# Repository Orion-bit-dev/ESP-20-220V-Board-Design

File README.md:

# 220V Power Monitor (ESP32)

An ESP32 project that switches two 220 V lamps with push buttons and a live web page, senses an outside 220 V power source, keeps working when WiFi drops, and lets me save a new WiFi network from my phone.

Built as part of my learning in programming and electronics. It builds on two earlier projects: a basic power monitor and a power-sensing relay with a web page.

---

## ⚠️ Safety first (220 V)

This project involves mains voltage, which can seriously injure or kill.

- **Never put 220 V on the breadboard or near the ESP32 and OLED.** Use the screw terminals of the relay modules only.
- Keep the whole 220 V side in a **closed enclosure**, with a **fuse or breaker** before it.
- Have a **qualified electrician** make the 220 V connections. Switch the power off at the breaker before touching anything.
- The ESP32 side runs at only 3.3 V and 5 V. That is the part I built myself.

---

## Features

- **Two relay outputs** switch two 220 V lamps (LED 1 and LED 2).
- **Physical push buttons** toggle each relay.
- **Live web page** shows the full state and refreshes every second (`/status` endpoint returning JSON).
- **OLED display** (I2C) shows the same state, plus the IP address for 3 seconds at boot.
- **Mains sensing** of an outside 220 V source ("Power 2") using an isolated supply and an opto module.
- **WiFi that doesn't freeze the device:** a non-blocking `millis()` timer reconnects every 15 seconds, so the buttons always work, even offline.
- **WiFi setup mode:** if no WiFi is saved, or I hold the setup button for 3 seconds, the ESP32 creates its own network (`ESP32_Setup`). I join it from my phone, open `192.168.4.1`, enter the new WiFi, and it saves to flash and restarts.
- **Admin password** required for the web Toggle buttons, since they switch 220 V.

### LED logic

| LED | Turns on when |
|---|---|
| LED 1 | Relay A is on **or** Power 2 is present |
| LED 2 | Relay B is on |

---

## Hardware

- ESP32 dev board
- 2 × 5 V relay modules (active low)
- 2 × push buttons (Relay A, Relay B) + 1 × setup button
- SSD1306 OLED, 128×64, I2C
- 100 µF capacitor
- HLK-PM01 (isolated 220 V to 5 V module)
- Opto-isolator module
- Fuse, enclosure, and two 220 V lamps

### Pin map (ESP32 side)

| Part | ESP32 pin |
|---|---|
| Relay A `IN` | D18 (relay `VCC` to VIN, `GND` to GND) |
| Relay B `IN` | D19 |
| Button A | D25 and GND |
| Button B | D26 and GND |
| Setup button | D32 and GND |
| Opto module output (Power 2 sense) | D27 and GND (LOW = present) |
| OLED | SDA D21, SCL D22, VCC 3V3, GND |
| Capacitor 100 µF | across 3V3 and GND (stripe leg to GND) |

### Sensing an outside 220 V source safely

```
220 V (Power 2) -> fuse -> HLK-PM01 (isolated 5 V module) -> opto module input (IN+ / IN-)
opto module output -> ESP32 D27 and GND
```

- Opto module jumper **ON** (3–12 V input).
- The HLK output minus goes **only to the opto IN-**, never to the ESP32 GND. The opto module is the isolation bridge.
- Do **not** use a bare opto module directly on 220 V, and never use a resistor or capacitor dropper supply.
- Alternative: a relay with a 220 V coil, with its dry contact wired to D27 and GND like a switch.

---

## Software

### Requirements

- Arduino IDE with the ESP32 board package
- Libraries: `Adafruit GFX Library` and `Adafruit SSD1306`
- Built-in ESP32 libraries used: `WiFi`, `WebServer`, `Preferences`, `Wire`

### Setup

1. Open `power_monitor_220v.ino` in the Arduino IDE.
2. **Change the placeholder passwords** at the top of the sketch:
   - `apPass`: the password of the setup WiFi (8 characters or more)
   - `adminPass`: the password needed for the web Toggle buttons
3. Select your ESP32 board and upload.
4. On first boot there is no saved WiFi, so the OLED shows **WIFI SETUP MODE**. Connect your phone to `ESP32_Setup`, open `192.168.4.1`, enter your WiFi name and password, and tap **Save & Reboot**.
5. After reboot, the OLED shows the IP address. Open it in a browser to see the live page.

> Never commit real WiFi names or passwords to a public repository.

### Web endpoints

| Endpoint | Method | Purpose |
|---|---|---|
| `/` | GET | Live status page (or the WiFi form in setup mode) |
| `/status` | GET | Current state as JSON |
| `/toggleA`, `/toggleB` | POST | Toggle a relay (needs the admin password) |
| `/savewifi` | POST | Save a new WiFi (works only in setup mode) |

---

## Security fixes from my first version

- Removed the fallback WiFi name and password from the code. With nothing saved, the device goes straight to setup mode.
- `/savewifi` now works only in setup mode. Before, anyone on my WiFi could overwrite my settings.
- The web Toggle buttons need the admin password, because they switch 220 V.
- Holding the setup button no longer restarts setup mode repeatedly.
- The OLED now also updates when I toggle from the web page.

---

## Test checklist

| Check | Expected result |
|---|---|
| Nothing saved yet | OLED shows WIFI SETUP MODE |
| Boot with saved WiFi | "Connecting to WiFi", then the IP for 3 s, then the normal screen |
| Web page | Updates every second, no `?` shown |
| Buttons A and B | Relay clicks, web page and OLED follow |
| Web Toggle, wrong admin password | "Not allowed", relay does not move |
| Web Toggle, right admin password | Relay toggles, OLED follows |
| Power 2 on and off | LED 1 follows, Serial prints the change |
| Router off for 15 s, then on | Serial prints "WiFi dropped!", then it reconnects |
| Hold setup button for 3 s | OLED shows setup instructions, relays turn off |
| Save a new WiFi in setup mode | Restarts and joins it |
| `/savewifi` in normal mode | "Only in setup mode" |
| Unplug and plug back in | Remembers the saved WiFi |

---

## What I learned

- **OLED static at boot:** the WiFi power spike crashed the screen. Fixed with a 100 µF capacitor and calling `display.begin()` again after the WiFi attempt.
- **Never use `WiFi.mode(WIFI_OFF)`:** it crashed my ESP32 (`xQueueSemaphoreTake`). Use `WIFI_STA` or `WIFI_AP` instead, and let the buttons work offline.
- **No `while` loop without a `millis()` timeout:** the ESP32 freezes if the router is off.
- **Active-low relays:** "off" means letting go of the pin (`OUTPUT_OPEN_DRAIN` with HIGH). A normal `digitalWrite(HIGH)` left the relay stuck on.
- **The web page `?` bug:** switching to `XMLHttpRequest` fixed it for me. `fetch()` worked on an earlier page, so the real cause is not proven and is worth testing again.
- **Keep secrets out of code:** I once had my real WiFi password in a sketch. Secrets don't belong in code, notes, or chats.

---

## Roadmap

- [ ] Add a password to the `/savewifi` page and show the IP in the setup screen
- [ ] Draw the schematic in KiCad, with a mains block (fuse, HLK-PM01) separated from the low-voltage block (opto module, relays, ESP32)
- [ ] Add photos of the build and wiring

---

## Disclaimer

This is a learning project, provided as is. Working with mains voltage is dangerous. Always involve a qualified electrician for the 220 V side, and use this at your own risk.

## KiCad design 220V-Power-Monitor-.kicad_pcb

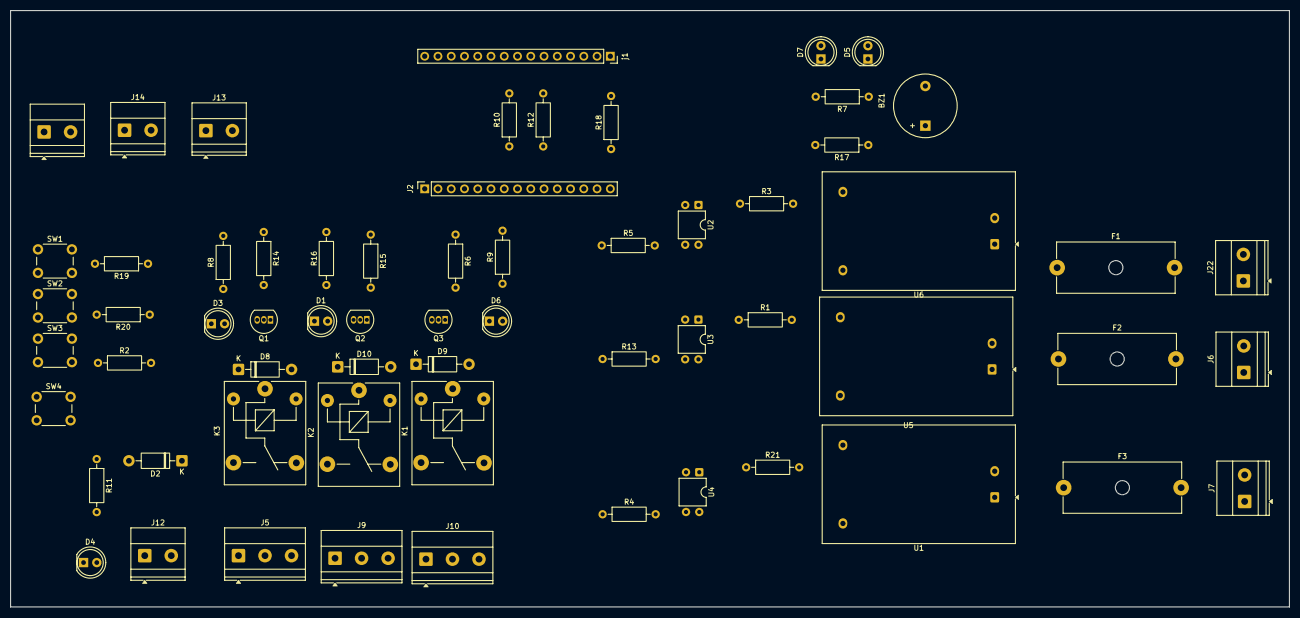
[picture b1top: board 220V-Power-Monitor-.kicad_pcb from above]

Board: 2 copper layers, 245.0 x 114.2 mm, 63 parts (0 on the bottom side), 52 nets, no tracks yet.

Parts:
BZ1: Buzzer; Buzzer_12x9.5RM7.6
D1, D3, D4, D5, D6, D7: LED; LED_D5.0mm
D2, D8, D9, D10: D; D_DO-41_SOD81_P10.16mm_Horizontal
F1, F2, F3: Fuse; Fuseholder_Cylinder-5x20mm_Schurter_0031_8201_Horizontal_Op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
J2: ESP32_left_row; PinSocket_1x15_P2.54mm_Vertical
J5, J9, J10: Screw_Terminal_01x03; TerminalBlock_Phoenix_MKDS-1,5-3-5.08_1x03_P5.08mm_Horizont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
J6, J7, J8, J12, J13, J14, J22: Screw_Terminal_01x02; TerminalBlock_Phoenix_MKDS-1,5-2-5.08_1x02_P5.08mm_Horizont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
K1, K2, K3: Relay_SPDT; Relay_SPDT_SANYOU_SRD_Series_Form_C
Q1, Q2, Q3: BC337; TO-92_Inline
R1, R2, R3, R19, R20, R21: 470; R_Axial_DIN0207_L6.3mm_D2.5mm_P10.16mm_Horizontal
R4, R5, R6, R13, R14, R15: 10k; R_Axial_DIN0207_L6.3mm_D2.5mm_P10.16mm_Horizontal
R7, R8, R9, R16, R17: 330; R_Axial_DIN0207_L6.3mm_D2.5mm_P10.16mm_Horizontal
R10, R11, R12, R18: 1k; R_Axial_DIN0207_L6.3mm_D2.5mm_P10.16mm_Horizontal
SW1, SW2, SW3, SW4: SW_Push; SW_PUSH_6mm
U1, U5, U6: HLK-PM01; Converter_ACDC_Hi-Link_HLK-PMxx
U2, U3, U4: PC817; DIP-4_W7.62mm
j1: ESP32_right_row; PinSocket_1x15_P2.54mm_Vertical

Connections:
/GND_ESP: BZ1.2 (-), D1.1 (K), D3.1 (K), D4.1 (K), D5.1 (K), D6.1 (K), D7.1 (K), J2.14, J8.2, J12.2, J13.2, J14.1, Q1.3 (E), Q2.3 (E), Q3.3 (E), R6.1, R14.1, R15.1, SW1.1, SW2.1, SW3.1, SW4.1, U2.3, U3.3, U4.3, j1.2
GND_ISO1: U2.2, U6.3 (-Vout)
GND_ISO2: U3.2, U5.3 (-Vout)
GND_ISO3: U1.3 (-Vout), U4.2
unnamed: BZ1.1 (+), j1.7
unnamed: D1.2 (A), R16.1
unnamed: D2.2 (A), J12.1, R11.1
unnamed: D3.2 (A), R8.1
unnamed: D4.2 (A), R11.2
unnamed: D5.2 (A), R7.2
unnamed: D6.2 (A), R9.1
unnamed: D7.2 (A), R17.2
unnamed: D8.2 (A), Q1.1 (C)
unnamed: D9.2 (A), Q3.1 (C)
unnamed: D10.2 (A), Q2.1 (C)
unnamed: D2.1 (K), D8.1 (K), D9.1 (K), D10.1 (K), J2.15
unnamed: J2.2, R4.2, U4.4
unnamed: J2.4, R5.2, U2.4
unnamed: J2.5, R13.2, U3.4
unnamed: J2.6, SW4.2
unnamed: J2.7, R9.2
unnamed: J2.8, R19.1, SW1.2
unnamed: J2.9, R20.2, SW2.2
unnamed: J2.10, R2.1, SW3.2
unnamed: J2.11, R8.2
unnamed: J2.13, R16.2
unnamed: J6.1, U5.2 (AC/N)
unnamed: F2.1, J6.2
unnamed: J7.1, U1.2 (AC/N)
unnamed: F3.2, J7.2
unnamed: J8.1, R19.2
unnamed: J13.1, R2.2
unnamed: J14.2, R20.1
unnamed: J22.1, U6.2 (AC/N)
unnamed: F1.2, J22.2
unnamed: Q1.2 (B), R10.1, R14.2
unnamed: Q2.2 (B), R12.1, R15.2
unnamed: Q3.2 (B), R6.2, R18.1
unnamed: R1.1, U3.1
unnamed: R3.1, U2.1
unnamed: R21.1, U4.1
unnamed: R21.2, U1.4 (+Vout)
unnamed: F3.1, U1.1 (AC/L)
unnamed: R1.2, U5.4 (+Vout)
unnamed: F2.2, U5.1 (AC/L)
unnamed: R3.2, U6.4 (+Vout)
unnamed: F1.1, U6.1 (AC/L)
unnamed: R4.1, R5.1, R13.1, R17.1, j1.1
unnamed: R7.1, j1.5
unnamed: R10.2, j1.9
unnamed: R12.2, j1.10
unnamed: R18.2, j1.15
